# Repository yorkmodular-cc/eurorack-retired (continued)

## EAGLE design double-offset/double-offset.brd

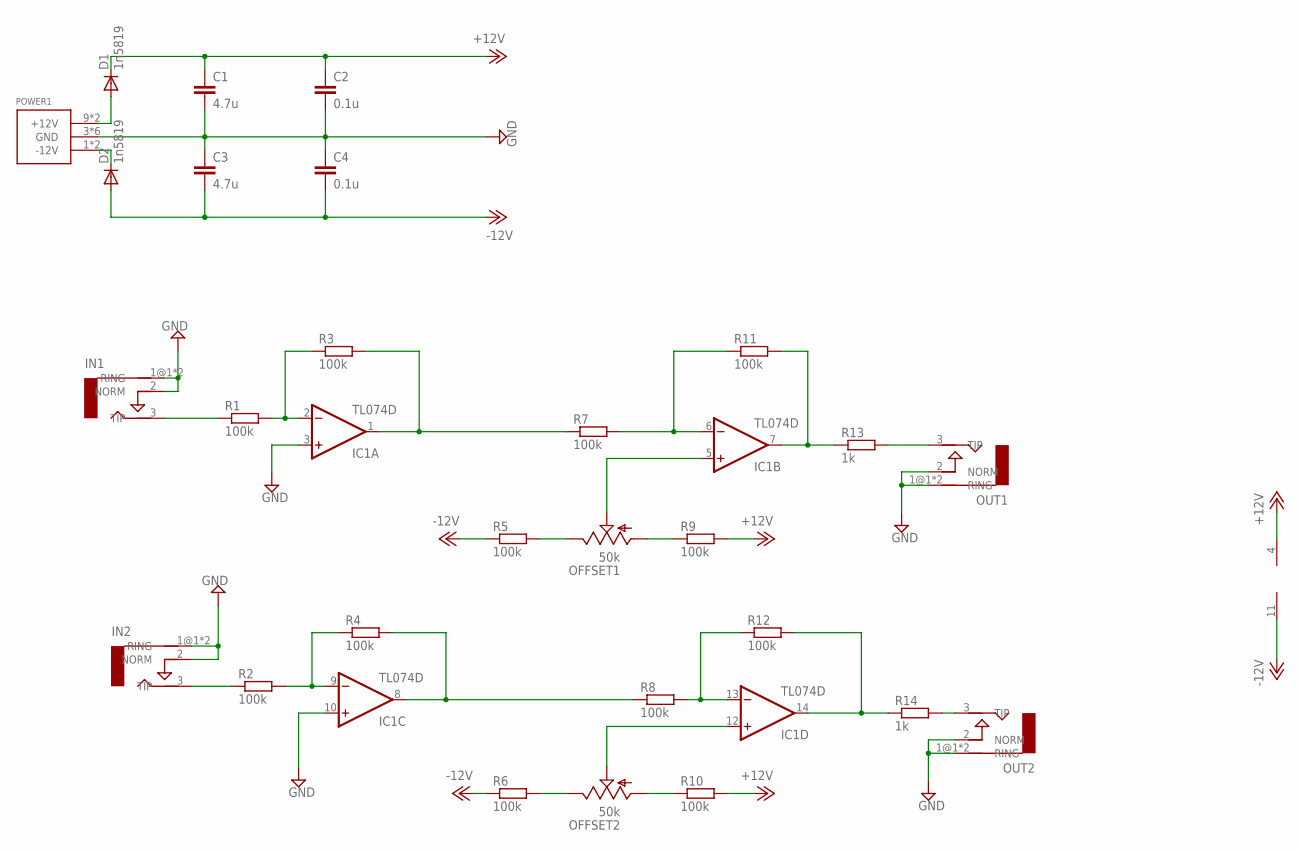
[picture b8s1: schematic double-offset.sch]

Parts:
C1, C3: 4.7u; C0805
C2, C4: 0.1u; C0805
D1, D2: 1n5819; SOD323-W
IC1: TL074D; SO14
IN1, IN2: AUDIO-JACKERTHENVAR; ERTHENVAR-JACK
OFFSET1, OFFSET2: 50k; 9MM_SNAP-IN_POT
OUT1, OUT2: AUDIO-JACKERTHENVAR; ERTHENVAR-JACK
POWER1: POWER_SIMPLE10; POWER_10
R1, R2, R3, R4, R5, R6, R7, R8, R9, R10, R11, R12: 100k; R0805
R13, R14: 1k; R0805

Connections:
+12V: C1.1, C2.1, D1.C, IC1.4 (V+), R9.2, R10.2
-12V: C3.2, C4.2, D2.A, IC1.11 (V-), R5.1, R6.1
GND: C1.2, C2.2, C3.1, C4.1, IC1.3 (+IN), IC1.10 (+IN), IN1.1@1 (RING), IN1.1@2 (RING), IN1.2 (NORM), IN2.1@1 (RING), IN2.1@2 (RING), IN2.2 (NORM), OUT1.1@1 (RING), OUT1.1@2 (RING), OUT1.2 (NORM), OUT2.1@1 (RING), OUT2.1@2 (RING), OUT2.2 (NORM), POWER1.3 (GND), POWER1.4 (GND), POWER1.5 (GND), POWER1.6 (GND), POWER1.7 (GND), POWER1.8 (GND)
unnamed: IC1.1 (OUT), R3.2, R7.1
unnamed: IC1.6 (-IN), R7.2, R11.1
unnamed: IC1.7 (OUT), R11.2, R13.1
unnamed: OUT1.3 (TIP), R13.2
unnamed: IC1.2 (-IN), R1.2, R3.1
unnamed: IC1.5 (+IN), OFFSET1.2 (S)
unnamed: IC1.13 (-IN), R8.2, R12.1
unnamed: IC1.14 (OUT), R12.2, R14.1
unnamed: IC1.8 (OUT), R4.2, R8.1
unnamed: IC1.9 (-IN), R2.2, R4.1
unnamed: D2.C, POWER1.1 (-12V), POWER1.2 (-12V)
unnamed: D1.A, POWER1.9 (+12V), POWER1.10 (+12V)
unnamed: IC1.12 (+IN), OFFSET2.2 (S)
unnamed: OUT2.3 (TIP), R14.2
unnamed: OFFSET1.3 (E), R5.2
unnamed: OFFSET1.1 (A), R9.1
unnamed: OFFSET2.3 (E), R6.2
unnamed: OFFSET2.1 (A), R10.1
unnamed: IN1.3 (TIP), R1.1
unnamed: IN2.3 (TIP), R2.1

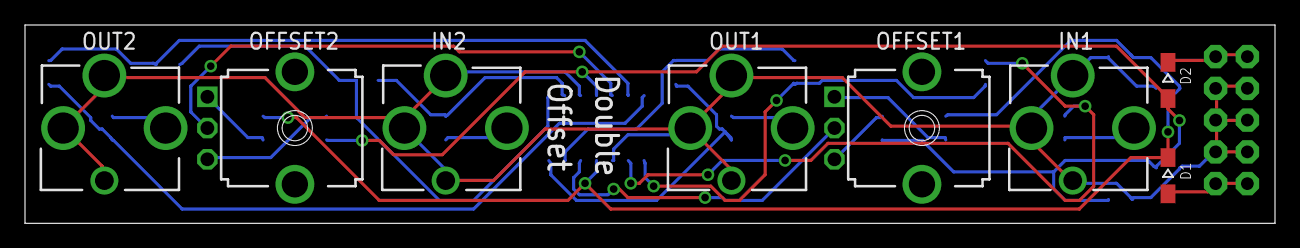
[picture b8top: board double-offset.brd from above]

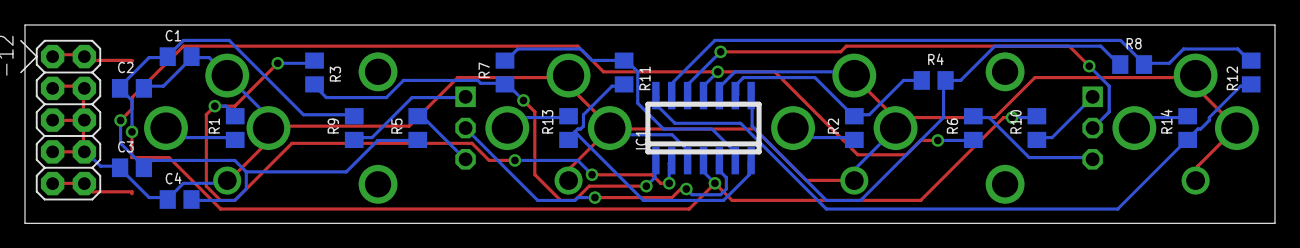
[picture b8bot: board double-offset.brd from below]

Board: 2 copper layers, 100.0 x 15.9 mm, 28 parts (20 on the bottom side), 23 nets.
